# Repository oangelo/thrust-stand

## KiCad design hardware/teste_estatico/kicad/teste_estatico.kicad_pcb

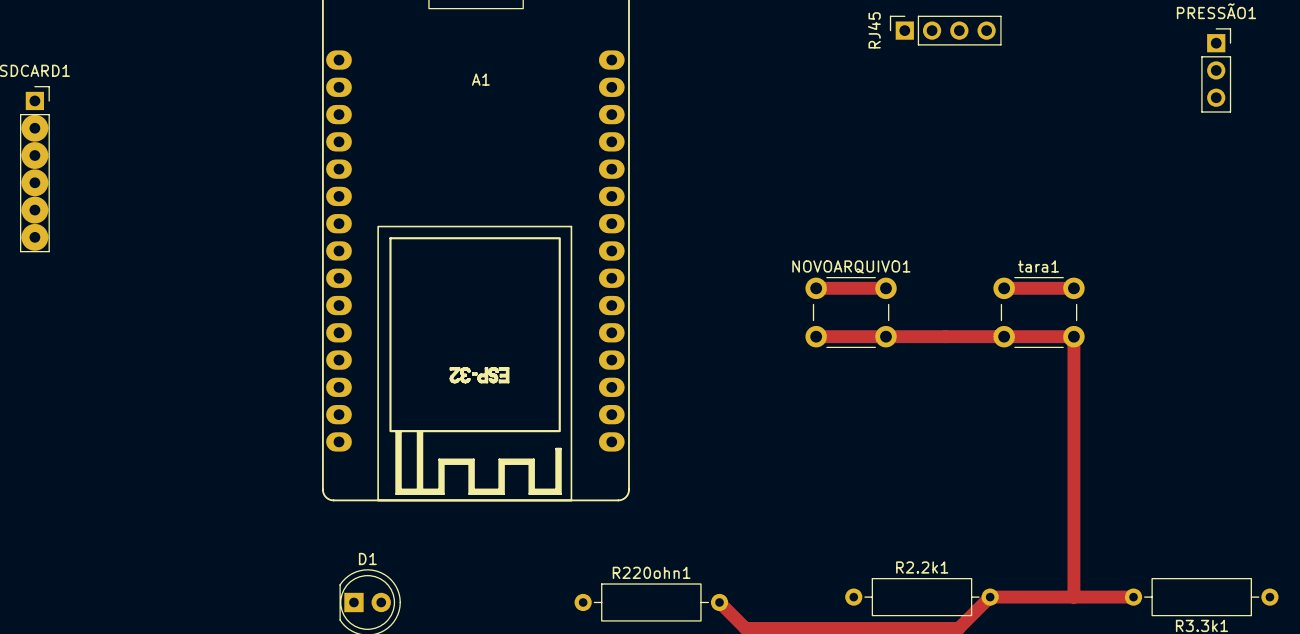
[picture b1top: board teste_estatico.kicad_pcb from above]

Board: 2 copper layers, 10 parts (0 on the bottom side), 15 nets.

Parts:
A1: ESP32_DevKit_V1_DOIT_30GPIOs; DOIT_ESP32_DEVKIT_30Pins
D1: LED; LED_D5.0mm_FlatTop
NOVOARQUIVO1: Push_Button; SW_PUSH_6mm
PRESSÃO1: Sensor de pressão; PinSocket_1x03_P2.54mm_Vertical
R2.2k1, R3.3k1, R220ohn1: R; R_Axial_DIN0309_L9.0mm_D3.2mm_P12.70mm_Horizontal
RJ45: conexão do rj45; PinSocket_1x04_P2.54mm_Vertical
SDCARD1: sd card; PinSocket_1x06_P2.54mm_Vertical
tara1: Push_Button; SW_PUSH_6mm

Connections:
unnamed: A1.21 (ADC1_CH4/D32), NOVOARQUIVO1.1
unnamed: A1.22 (ADC1_CH4/D32), tara1.1
unnamed: A1.20 (ADC1_CH7/D35), A1.29 (GND), NOVOARQUIVO1.2, R2.2k1.2, R3.3k1.2, R220ohn1.2, RJ45.1, tara1.2
unnamed: A1.25 (ADC2_CH7/D27), RJ45.2
unnamed: A1.5 (D4/ADC2_CH0), D1.1 (K)
unnamed: A1.8 (D5), SDCARD1.6
unnamed: A1.10 (D19), SDCARD1.3
unnamed: A1.15 (D23), SDCARD1.4
unnamed: A1.24 (DAC2/ADC2_CH9/D26), RJ45.3
unnamed: A1.2 (GND), SDCARD1.1
unnamed: A1.6 (RX2/GPIO16), SDCARD1.5
unnamed: A1.30 (VIN), PRESSÃO1.2, RJ45.4, SDCARD1.2
unnamed: D1.2 (A), R220ohn1.1
unnamed: PRESSÃO1.1, R2.2k1.1
unnamed: PRESSÃO1.3, R3.3k1.1

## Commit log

2026-05-06 Add LittleFS fallback for storage, remove RTC module
2026-05-09 Atualiza projeto KiCad
2026-05-11 adcionado arquivos pcb fusion 360
2026-05-11 adcionado atulização nos arquivos de pcb kicad
2026-06-10 HOTFIX
2026-06-15 docs: adiciona AGENTS.md com guia de estilo e comandos de build
    Instruções para agentes de IA cobrindo: comandos de build/upload do firmware Arduino/ESP32, execução de ferramentas Python, convenções de código C++ e Python, organização do repositório e armadilhas 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
2026-06-15 docs: reorganiza fotos da caixa v1 e limpa backups do KiCad
    - Move fotos da caixa para docs/imagens/ com nomes normalizados
    - Remove backups automáticos do KiCad do versionamento
    - Adiciona *-backups/ e *.kicad_prl ao .gitignore
2026-06-15 docs: adiciona fotos da caixa v2
2026-06-15 docs: adiciona foto da caixa v1 com rolamentos
2026-06-15 docs: adiciona fotos da caixa v3
2026-06-15 docs: adiciona documentação da evolução da caixa de teste
    Documenta as 3 versões da estrutura física:
    - V1: perfil V-slot 20x20mm (alumínio) — protótipo, cara e frágil
    - V2: metalon 20x20mm (aço) — trapezoidal, abandonada (solda torta)
    - V3: tubo 1" x 1/4" (aço) — atual, com trilhos lineares
2026-06-15 docs: corrige material da v3 — cantoneira, não tubo
2026-06-15 docs: atualiza AGENTS.md com convenções de imagens e remotes
2026-06-15 hardware: adiciona STEP da caixa v3
2026-06-16 docs: adiciona documentação detalhada da bancada v3
    - Especificações da célula de carga SZ51X-500kg (PESO)
    - Sistema de guia linear (eixo ⌀12mm, rolamento SC12UU)
    - Resolução estimada: ~0,5N em 4,9kN
    - 4 fotos de componentes
2026-06-16 docs: comprime imagens para 1200px e remove EXIF
    Reduzido de 34MB para 1.2MB (96% de redução).
    - Redimensionado para 1200px largura
    - Qualidade JPEG 80
    - Metadados EXIF removidos
2026-06-16 docs: formata imagens com tabelas HTML e click-to-zoom
    - Imagens em tabelas HTML para layout lado a lado (3 por linha)
    - Imagens isoladas para renders e documentos importantes
    - Largura: 300px (tabelas) e 500px (isoladas)
    - Click-to-zoom nativo do GitHub
2026-06-16 docs: adiciona foto do mancal SC12UU e corrige labels da guia linear
    - Adiciona foto do mancal SC12UU (isolado, 400px)
    - Corrige labels: ambas as imagens são da guia linear (montada e solta)
    - Remove arquivo 'content' temporário
2026-06-16 docs: reorganiza V3_DETALHES.md e corrige nomenclatura SK12/SC12UU
    - Renomeia v3_mancal_sc12uu.jpg → v3_sk12_mancal.jpg (mancal/suporte de eixo)
    - Renomeia v3_rolamento_sc12uu.jpg → v3_sc12uu_pillow_block.jpg (rolamento linear)
    - Adiciona v3_sk12_eixos.jpg (mancal com eixos lineares)
    - Reorganiza documento por componente (guia linear → célula → resolução)
    - Remove seção 'Fotos' separada, specs e fotos juntas por componente
2026-06-16 docs: coloca fotos do SK12 lado a lado na seção de guia linear
2026-06-16 docs: rotaciona imagens da v3
2026-06-16 docs: adiciona specs de fixação do Pillow Block SC12UU
2026-06-16 docs: adiciona referência ao modelo STEP na documentação v3
2026-06-16 docs: atualiza AGENTS.md com convenções de imagens e V3_DETALHES.md
2026-06-22 docs: adiciona vídeos de teste estático V1 e V2
    - Move vídeos da raiz para docs/videos/ com nomes descritivos
    - Configura Git LFS para arquivos .mp4
    - Adiciona seções de vídeo em EVOLUÇÃO_CAIXA.md (V1 e V2)
    - Atualiza AGENTS.md com convenção de vídeos
2026-06-22 docs: usa tag <video> para playback inline no GitHub
2026-06-22 docs: usa AVIF animado para playback inline de vídeos
    - Converte vídeos de teste estático para AVIF (500px, 15fps)
    - V1: 334 KB, V2: 319 KB (vs 2.4 MB e 9.7 MB originais)
    - Embed com sintaxe ![alt](./imagens/file.avif) no GitHub
    - Mantém links para MP4 originais com áudio
    - Atualiza AGENTS.md com convenção de conversão SVT-AV1
2026-06-22 docs: ajusta largura dos vídeos AVIF para 300px
2026-06-23 docs: adiciona convenção de armazenamento de dados de teste
    - Remove pastas de backup redundantes (hardware/teste_estatico/*-backups/)
    - Adiciona fp-info-cache ao .gitignore
    - README.md: seção 'Dados de Teste' apontando para Serra-Rocketry/motor
    - AGENTS.md: seção 'Data Storage Conventions' definindo onde armazenar dados
